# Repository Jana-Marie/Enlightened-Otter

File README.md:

# Enlightened-Otter

Enlightened-Otter is an Open-Source and OSHW work-light for hacker/maker events like the chaos communication congress. It is based upon a STM32F334 with its 
high resolution timer as dual boost 
converter. The main goal is to provide cordless, high CRI, high brightness, flicker-free illumination with a variable color temperature. This is achieved by using LEDs with high a CRI (>93, STW9Q14C) and 
the boost 
converter operating at a frequency of up to 850khz. The PCB also features USB-C (power profile 1) to deliver enough power to charge the 18650 type batteries as well as keep up operation of the boost converter.

Enlightened-Otter can be screwed onto an empty bottle of Mate (or similar), therefore serving with a very small footprint.

## Specs

|								| Typical Value |
| -------------------------		| -------------	|
| I*out* (per channel)	 		| 0-500mA 		|
| V*out* (per channel)			| 0-18.5V 		|
| P*out* (per channel)			| 0-7.5W*		|
| Illuminance (3500k @400mA)	| 1600lx*  		|
| Illuminance (6500k @400mA)	| 2000lx* 		|
| V*in* (USB) 					| 4.8-14V  		|
| I*in* (USB) 					| 3A  			|
| V*bat* 						| 3.8V 			|
| I*bat* (max)					| 5A  			|
| Boost frequency				| 500khz**		|
| I*ripple* (@2.5kHz)			| < 0.5mA 		|

\* Needs to be measured again
 
\** Needs to be evaluated again

## Building and flashing

Change *Inc/defines.h* to fit your desires, then build with

`make clean all`

and flash it via Ozone or st-utils

`st-flash --reset write build/*.bin 0x8000000`

## Images V2.1

## Images V2.0

## Images V1.1

## Videos

Click to play

#### On a Bottle

#### Boost converter operation

#### TSC operation

#### LED brightness test

## Known Bugs

- Touch does not work when licked (tested by @NiklasFauth)
	- Workaround: Do not lick PCB

## Planning

### Folder structure

- **Src/** : Contains the source files to build the firmware
- **Drivers/** : Contains the STM library files
- **Inc/** : Contains the header files as well as the customization file for the firmare
- **Tools/** : Contains python scripts to generate specific code
- **HW/** : Contains the Schematic, Gerber and other Hawrdware files
- **Images/** : Contains the images used in this repo
- **3D Files/** : Contains the 3D file to be printed as inlet as well as its source
- **/** : Contains other build files e.g. Makefile, linkerscript

### Current state:

PCB V2.1 is here, V2.11 is ordered.

Complete power redesign. HW is flashable, both boost converter work properly up to a current of ~500mA, current regulation works on both boost converters ( < +-0.5mA up to 500mA, regulation frequency is 2.5khz), RT9466 seems to do its job, does work properly on 
batteries, not on USB. Measuring thought the RT does not work, Power down does. LED outputs and Touch inputs work, has correct fault handling.
Advanced User interface is also working, current and color can be set via touch input. Soft on/off works fine. Gamma correcture is applied.
The whole PCB can be shut down by holding the power button.

HW regulates after boot while main loop is basically empty \o/

### To do:

- [ ] measuring throught the RT does not work
- [ ] ADC1 wrong values -> investigate
- [ ] test esp8266
- [ ] implement esp8266
- [ ] visualize battery voltage -> moodlight LEDs
- [ ] Overtemp protection
- [ ] Find more to do's

### Done:

- [x] Implement moodlight LEDs
- [x] touch slider is not super responsive -> investigate
- [x] "Mobile handling"
	- [x] Touch is not that responsive
	- [x] Added filters to touch input
	- [x] Battery low alarm/turnoff -> is implemented, doesnt work, see RT9466 measuring
- [x] everything is super slow when Itarget is 0.0 -> investigate
- [x] UVP
- [x] Port firmware to V2.1
- [x] RT cannot be turned off or cannot charge batteries - investigate
- [x] Optimize code
	- [x] make it less ugly
	- [x] now make it faster
- [x] Test I2C - broken?
	- writing works, reading is buggy, switch to dma
	- [x] implemented DMA
	- [x] Receiving data does not work properly, data is present but not written into the variable
		- switched msb and lsb -.-
- [x] rewrite gamma correction
	- [x] use old one, but interpolate between points
		- didnt work properly, will do later
	- [x] Test it
- [x] find MPP
	- is at ~500khz
- [x] Fix regulator above 180mA
	- is flickering quite alot above 180mA
	- [x] Rewrite regulation, seems to be flickering
		- was gamma correction causing that problem
- [x] HW
	-  See HW/README.md
- [x] Make user Interface more responsive
- [x] Order new PCB (V1.1)
- [x] 3D Design
- [x] get rid of flicker at 0.5-2.5mA 
- [x] temperature calculation
- [x] get rid of global variables
	- moved them into structs
- [x] make the code more Timer/Interrupt based
	- [x] HRTIM
	- [x] HRTIM FLT
	- [x] ADC
	- [x] TSC
	- [x] I2C/UART
	- [x] Regulator
	- [x] UI
- [x] gamma correction
	- [x] write tool to generate gamma correction curve
	- [x] Implement it
	- [x] Test/debug it
- [x] Fix the HRTIM FLT1 line
- [x] Test Injected ADC
	- [x] ADC tested and seems to work just fine
	- [x] Add moving average filter to smooth out ADC values
	- [x] Add JEOC Interrupt
- [x] current calculation
- [x] Fix/write TSC controller
	- [x] Add second TSC bank
	- [x] Make it interrupt based
		- [x] write code
		- [x] Test that
- [x] Fix I2C timing/Interrupt issue
- [x] Get HRTIM to run
- [x] Get the LED's to light up
- [x] Write regulator
	- [x] Write simple, working I regulator
	- [x] Make it cycle time independent
	- [x] Make regulator interrupt based
	- [x] Write a better PI regulator
- [x] Basic TSC,UART,DAC,COMP,I2C and GPIO functionality
- [x] Write the user interface
	- [x] Make it usable
- [x] Readout of touchslider
- [x] Be an otter
- [x] PCB does not burn

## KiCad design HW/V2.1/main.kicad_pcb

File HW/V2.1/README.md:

### Assemby instructions

Everything can be assembled as per manufacturer except for the following parts.

 - LED1,LED2,LED3 are per BOM sidemounted LEDs but they have to be rotated by 90 degrees and treated as reverse mount leds.
 - The studs cannot stand by themselfes, thus they have to be supported while reflowing
 - D7,D8 are normal 0805 LEDs but also reverse mounted
 
 - After reflowing the batteries can be inserted, EO should boot up and the middle led should light up. EO can now be flashed via Tag-connect
 - before adding the LED pcb it is mandatory to turn off EO!
 - Insulating washers (TO220 isolators) have to be added to all studs except for the GND stud, a non isolating washer has to be addded here
 - Use conducting screws and don't tightem them too much, try to reduce stress introduced into the pcb

### Changelog HW 2.11:

- re-routed everything, this time with good power design
- made pads for studs larger in diameter
- switched to kicad

### Todo list

- [x] SW 2.1
- [ ] SW 2.11
- [ ] Test LEDS and ESP
  - [x] LEDS
  - [ ] ESP

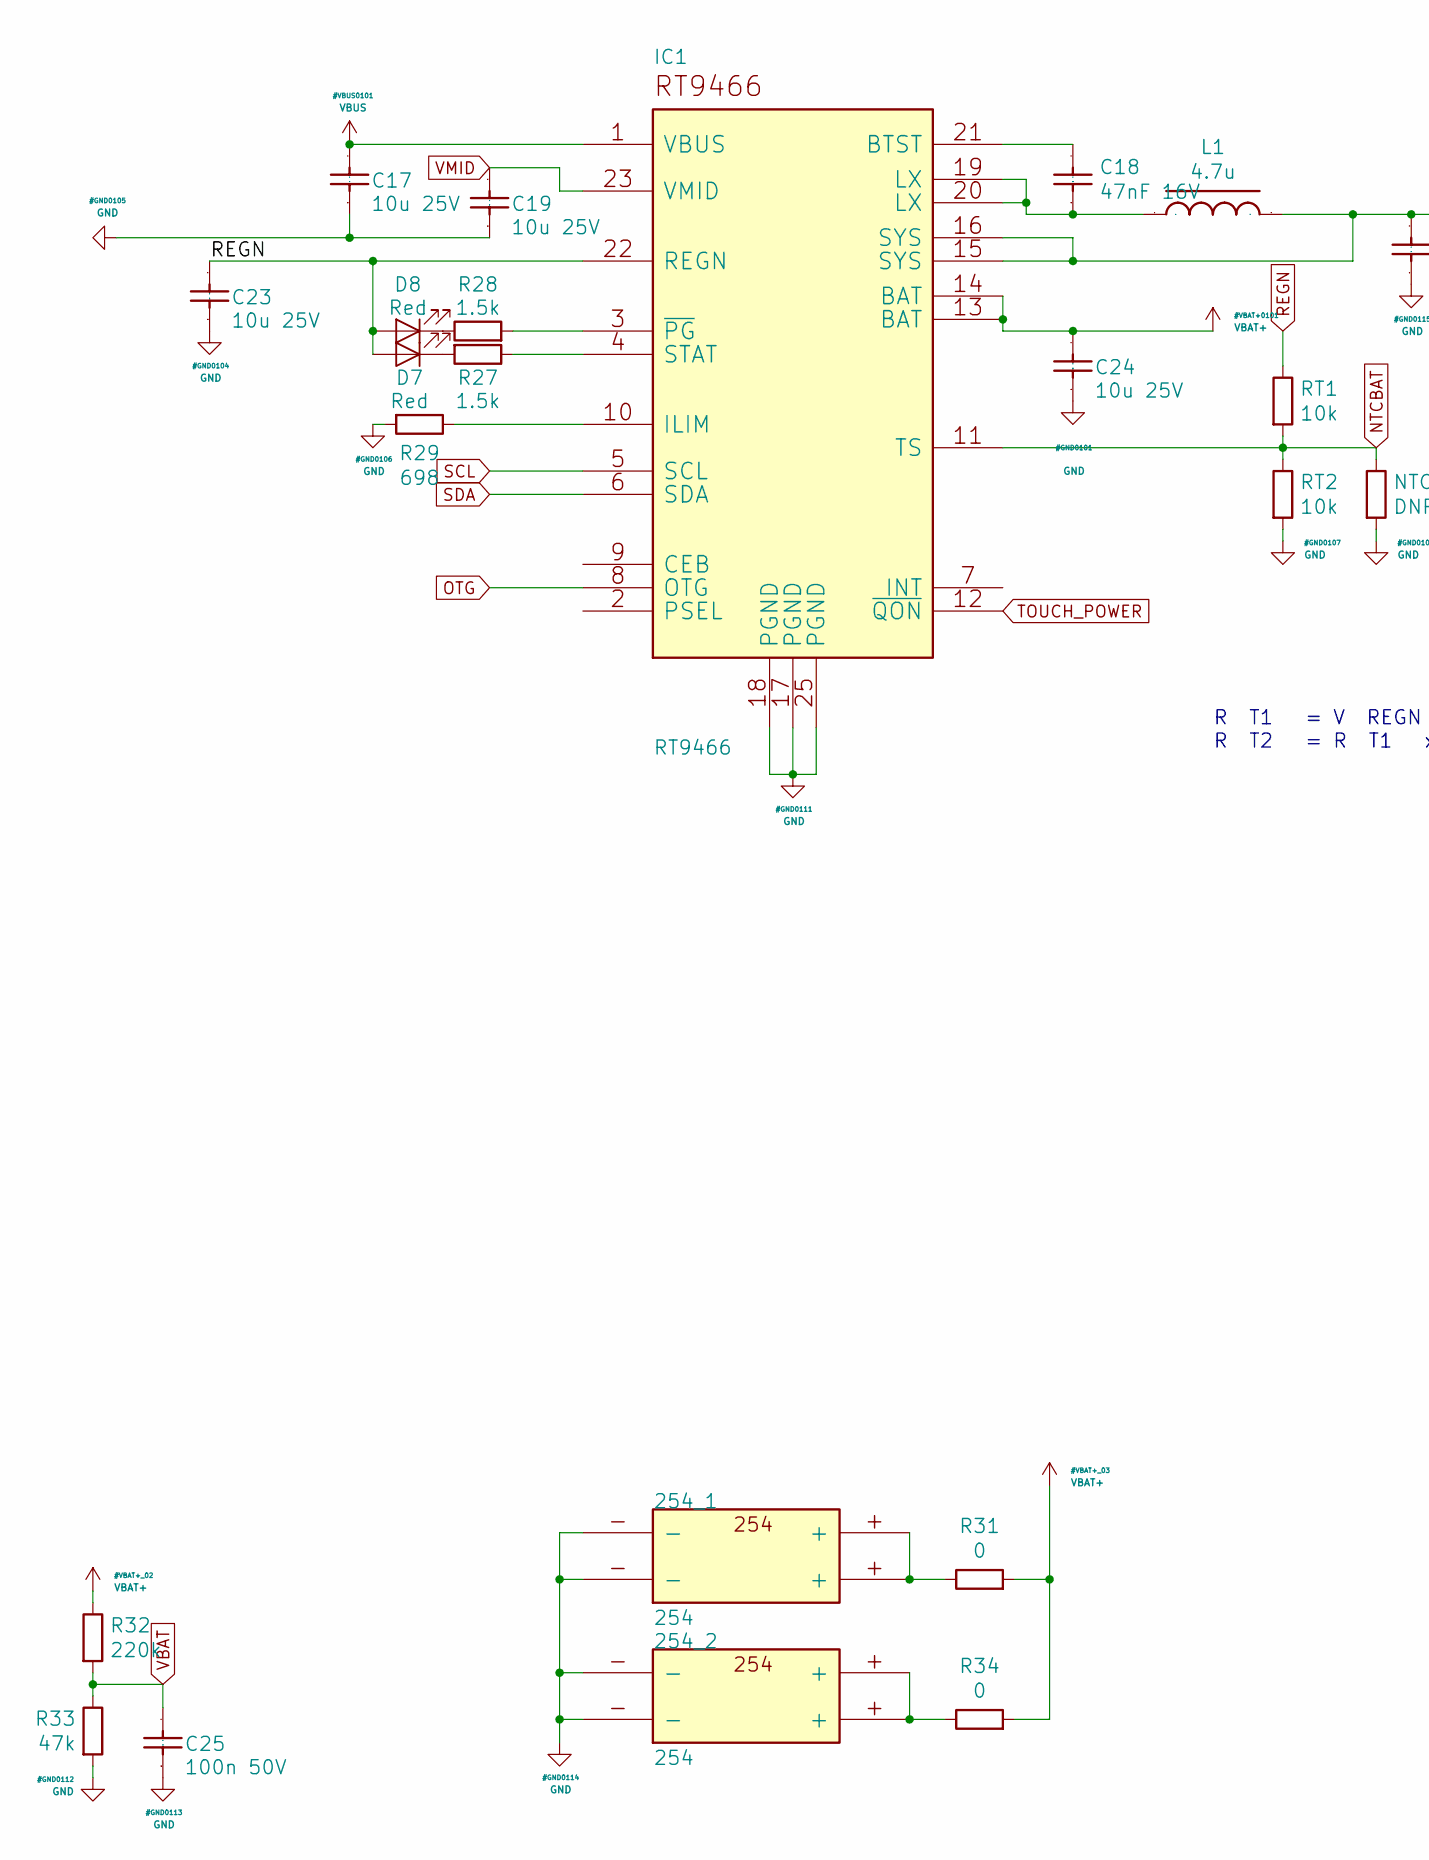
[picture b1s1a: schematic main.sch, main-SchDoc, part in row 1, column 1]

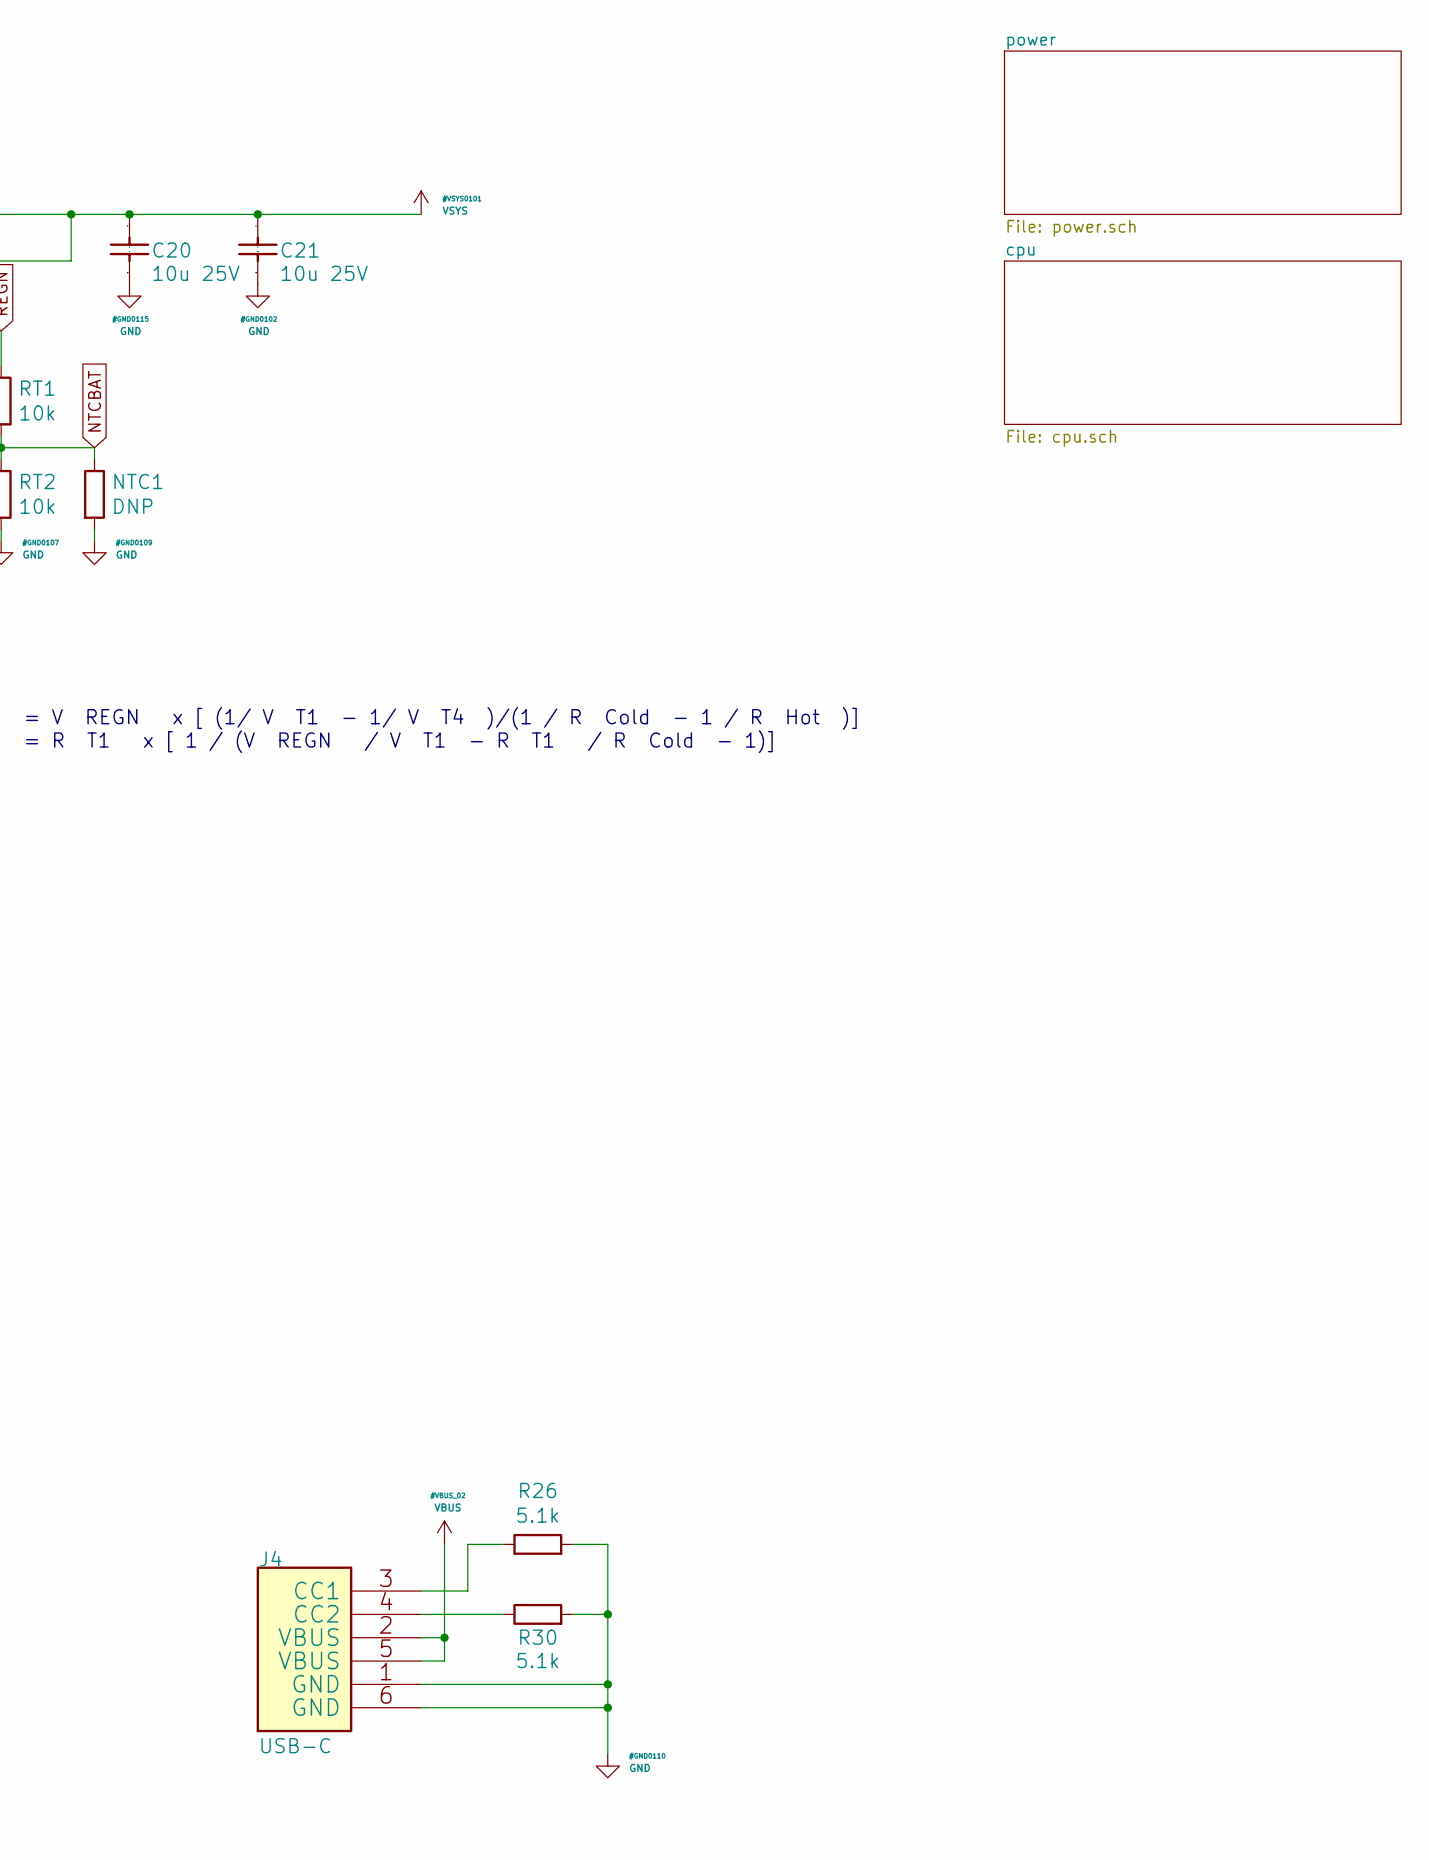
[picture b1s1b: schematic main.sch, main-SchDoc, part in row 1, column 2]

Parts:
254_1, 254_2: 254
C17, C19, C20, C21, C23, C24: 10u 25V; C_0805_2012Metric
C18: 47nF 16V; C_0603_1608Metric
C25: 100n 50V; C_0603_1608Metric
D7, D8: Red; LED_Reverse
IC1: RT9466; QFN-24-1EP_4x4mm_P0.5mm_EP2.6x2.6mm
J4: USB-C; USB-C_Power
L1: 4.7u; L_Taiyo-Yuden_MD-4040
NTC1: DNP; R_0603_1608Metric
R26, R30: 5.1k; R_0603_1608Metric
R27, R28: 1.5k; R_0603_1608Metric
R29: 698; R_0805_2012Metric
R31, R34: 0; R_1206_3216Metric
R32: 220k; R_0603_1608Metric
R33: 47k; R_0603_1608Metric
RT1, RT2: 10k; R_0603_1608Metric

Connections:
GND: 254_1.-, 254_2.-, C17.1, C19.1, C20.1, C21.1, C23.1, C24.1, C25.1, IC1.17 (PGND), IC1.18 (PGND), IC1.25 (PGND), J4.1 (GND), J4.6 (GND), NTC1.2, R26.2, R29.2, R30.2, R33.2, RT2.2; also elsewhere on the board
NTCBAT: IC1.11 (TS), NTC1.1, RT1.2, RT2.1
unnamed: 254_1.+, R31.1
unnamed: 254_2.+, R34.1
unnamed: C18.1, IC1.19 (LX), IC1.20 (LX), L1.1
unnamed: C18.2, IC1.21 (BTST)
unnamed: D7.1 (K), R27.2
unnamed: D8.1 (K), R28.1
unnamed: IC1.3 (~PG), R28.2
unnamed: IC1.4 (STAT), R27.1
unnamed: IC1.10 (ILIM), R29.1
unnamed: J4.3 (CC1), R26.1
unnamed: J4.4 (CC2), R30.1
OTG: IC1.8 (OTG); also elsewhere on the board
REGN: C23.2, D7.2 (A), D8.2 (A), IC1.22 (REGN), RT1.1
SCL: IC1.5 (SCL); also elsewhere on the board
SDA: IC1.6 (SDA); also elsewhere on the board
TOUCH_POWER: IC1.12 (~QON); also elsewhere on the board
VBAT: C25.2, R32.2, R33.1; also elsewhere on the board
VBAT+: C24.2, IC1.13 (BAT), IC1.14 (BAT), R31.2, R32.1, R34.2; also elsewhere on the board
VBUS: C17.2, IC1.1 (VBUS), J4.2 (VBUS), J4.5 (VBUS)
VMID: C19.2, IC1.23 (VMID); also elsewhere on the board
VSYS: C20.2, C21.2, IC1.15 (SYS), IC1.16 (SYS), L1.2; also elsewhere on the board

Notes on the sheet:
R T1 = V REGN x [ (1/ V T1 - 1/ V T4 )/(1 / R Cold - 1 / R Hot )]
R T2 = R T1 x [ 1 / (V REGN / V T1 - R T1 / R Cold - 1)]

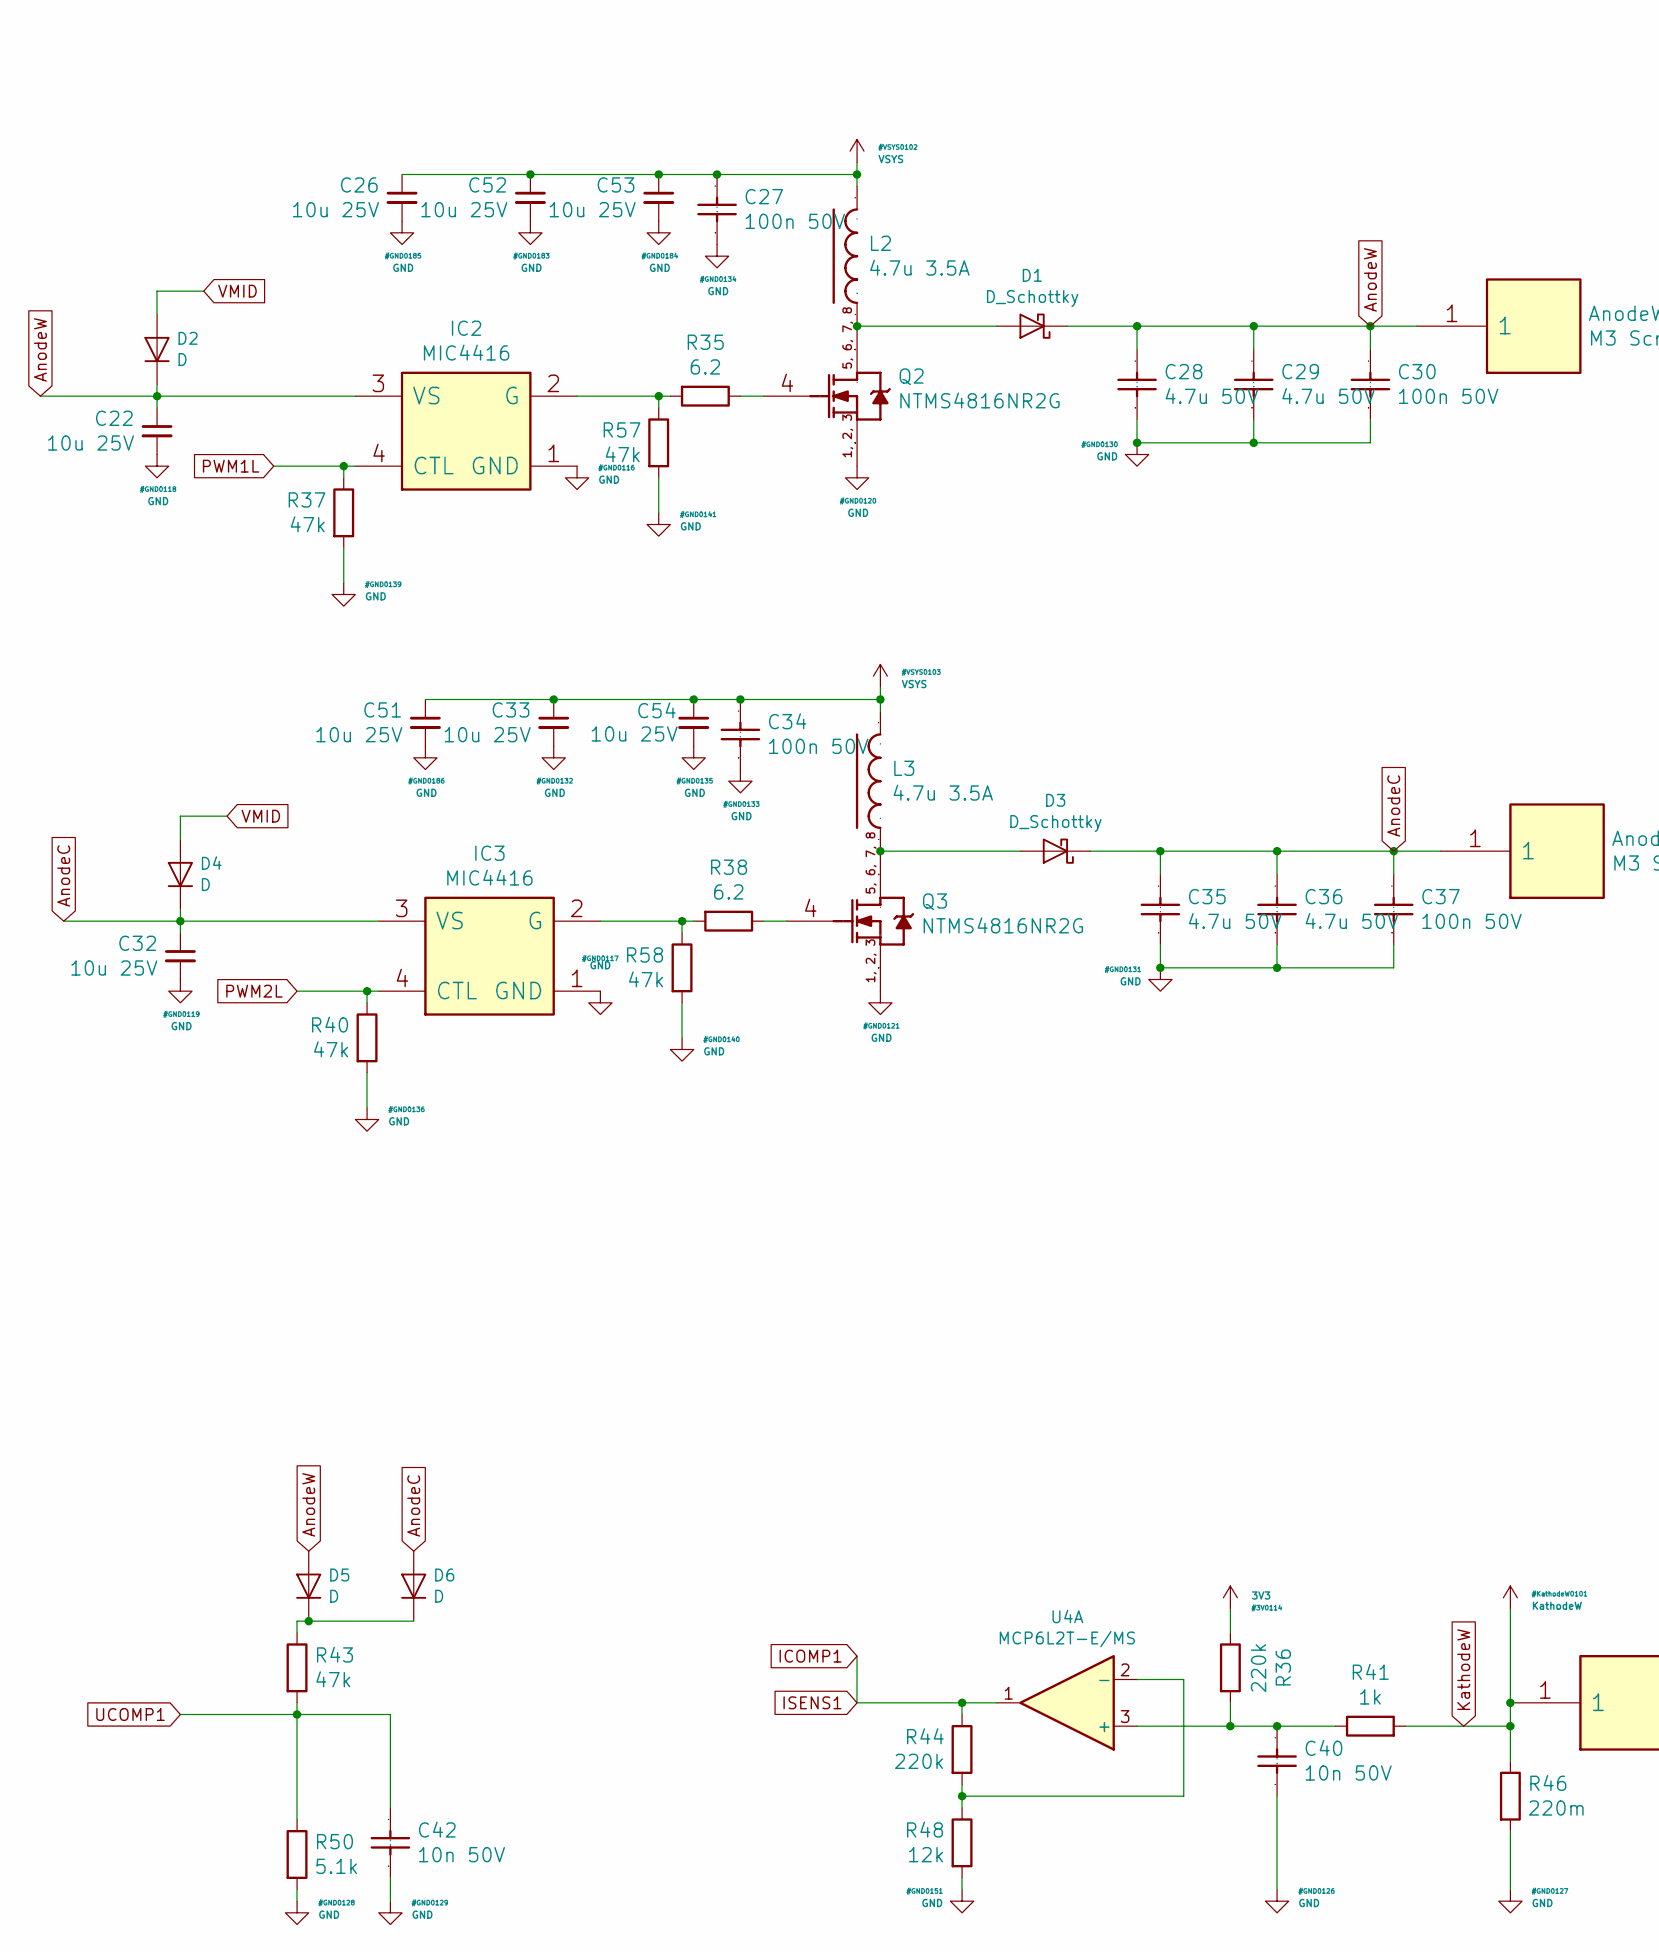
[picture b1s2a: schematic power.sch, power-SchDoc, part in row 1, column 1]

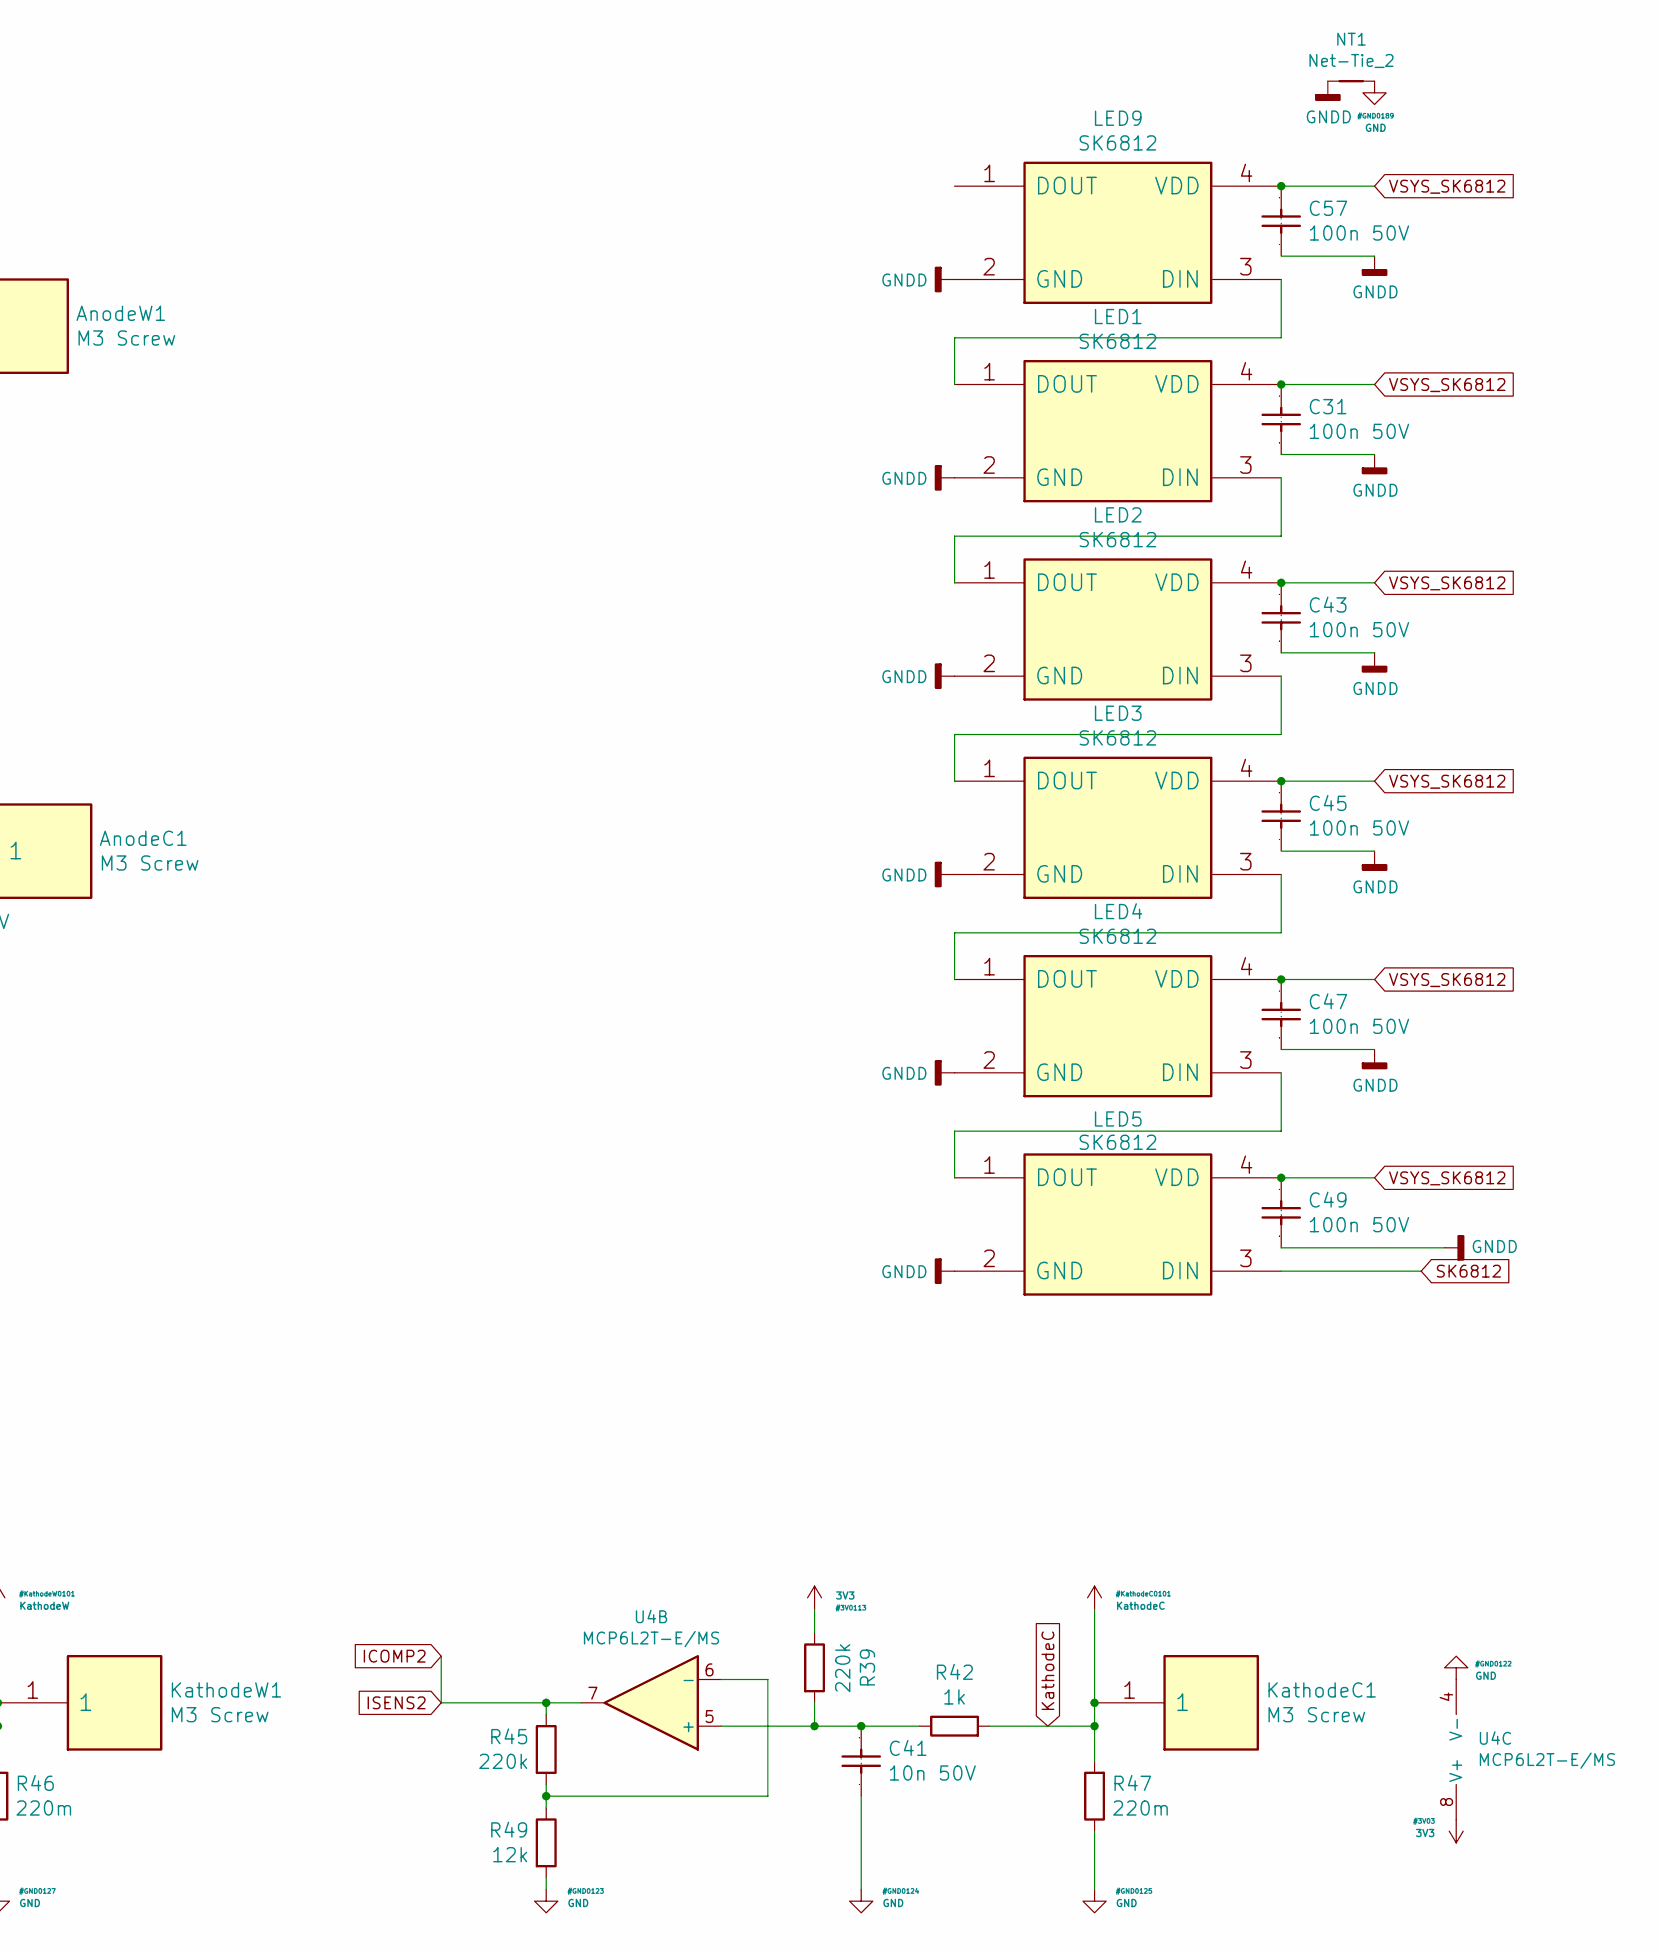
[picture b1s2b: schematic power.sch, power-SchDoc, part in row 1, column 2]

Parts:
AnodeC1: M3 Screw; M3_Screw
AnodeW1: M3 Screw; M3_Screw
C22, C26, C32, C33, C51, C52, C53, C54: 10u 25V; C_0805_2012Metric
C27, C30, C31, C34, C37, C43, C45, C47, C49, C57: 100n 50V; C_0603_1608Metric
C28, C29, C35, C36: 4.7u 50V; C_1206_3216Metric
C40, C41, C42: 10n 50V; C_0603_1608Metric
D1, D3: D_Schottky; D_SMA
D2, D4, D5, D6: D; D_SOD-123F
IC2, IC3: MIC4416; SOT-143
KathodeC1: M3 Screw; M3_Screw
KathodeW1: M3 Screw; M3_Screw
L2, L3: 4.7u 3.5A; L_Taiyo-Yuden_MD-4040
LED1, LED2, LED3, LED4, LED5, LED9: SK6812; sk6812mini
NT1: Net-Tie_2; NetTie-2_SMD_Pad0.5mm
Q2, Q3: NTMS4816NR2G; SO-8_3.9x4.9mm_P1.27mm
R35, R38: 6.2; R_0603_1608Metric
R36, R39, R44, R45: 220k; R_0603_1608Metric
R37, R40, R43, R57, R58: 47k; R_0603_1608Metric
R41, R42: 1k; R_0603_1608Metric
R46, R47: 220m; R_0603_1608Metric
R48, R49: 12k; R_0603_1608Metric
R50: 5.1k; R_0603_1608Metric
U4: MCP6L2T-E/MS; MSOP-8_3x3mm_P0.65mm

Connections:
3V3: R36.1, R39.1, U4.8 (V+); also elsewhere on the board
AnodeC: AnodeC1.1, C32.1, C35.2, C36.2, C37.2, D3.1 (K), D4.1 (K), D6.2 (A), IC3.3 (VS)
AnodeW: AnodeW1.1, C22.1, C28.2, C29.2, C30.2, D1.1 (K), D2.1 (K), D5.2 (A), IC2.3 (VS)
GND: C22.2, C26.2, C27.1, C28.1, C29.1, C30.1, C32.2, C33.2, C34.1, C35.1, C36.1, C37.1, C40.1, C41.1, C42.1, C51.2, C52.2, C53.2, C54.2, IC2.1 (GND), IC3.1 (GND), NT1.2, Q2.1 (S), Q2.2 (S), Q2.3 (S), Q3.1 (S), Q3.2 (S), Q3.3 (S), R37.2, R40.2, R46.2, R47.1, R48.2, R49.2, R50.2, R57.2, R58.2, U4.4 (V-); also elsewhere on the board
GNDD: C31.1, C43.1, C45.1, C47.1, C49.1, C57.1, LED1.2 (GND), LED2.2 (GND), LED3.2 (GND), LED4.2 (GND), LED5.2 (GND), LED9.2 (GND), NT1.1
ICOMP1: R44.1, U4.1; also elsewhere on the board
ICOMP2: R45.1, U4.7; also elsewhere on the board
KathodeC: KathodeC1.1, R42.2, R47.2
KathodeW: KathodeW1.1, R41.2, R46.1
unnamed: C40.2, R36.2, R41.1, U4.3 (+)
unnamed: C41.2, R39.2, R42.1, U4.5 (+)
unnamed: D1.2 (A), L2.1, Q2.5 (D), Q2.6 (D), Q2.7 (D), Q2.8 (D)
unnamed: D3.2 (A), L3.1, Q3.5 (D), Q3.6 (D), Q3.7 (D), Q3.8 (D)
unnamed: D5.1 (K), D6.1 (K), R43.1
unnamed: IC2.2 (G), R35.2, R57.1
unnamed: IC3.2 (G), R38.2, R58.1
unnamed: LED1.1 (DOUT), LED9.3 (DIN)
unnamed: LED1.3 (DIN), LED2.1 (DOUT)
unnamed: LED2.3 (DIN), LED3.1 (DOUT)
unnamed: LED3.3 (DIN), LED4.1 (DOUT)
unnamed: LED4.3 (DIN), LED5.1 (DOUT)
unnamed: Q2.4 (G), R35.1
unnamed: Q3.4 (G), R38.1
unnamed: R44.2, R48.1, U4.2 (-)
unnamed: R45.2, R49.1, U4.6 (-)
PWM1L: IC2.4 (CTL), R37.1; also elsewhere on the board
PWM2L: IC3.4 (CTL), R40.1; also elsewhere on the board
SK6812: LED5.3 (DIN); also elsewhere on the board
UCOMP1: C42.2, R43.2, R50.1; also elsewhere on the board
VMID: D2.2 (A), D4.2 (A); also elsewhere on the board
VSYS: C26.1, C27.2, C33.1, C34.2, C51.1, C52.1, C53.1, C54.1, L2.2, L3.2; also elsewhere on the board
VSYS_SK6812: C31.2, C43.2, C45.2, C47.2, C49.2, C57.2, LED1.4 (VDD), LED2.4 (VDD), LED3.4 (VDD), LED4.4 (VDD), LED5.4 (VDD), LED9.4 (VDD); also elsewhere on the board
